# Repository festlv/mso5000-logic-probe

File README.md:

# MSO5000 logic analyzer probe

This project aims to be a somewhat lower performance but significantly cheaper alternative to Rigol's PLA2216 
logic analyzer probe for MSO5000-series oscilloscopes.

The project is based on the design published by Gandalf_Sr on [EEVBlog forum](https://www.eevblog.com/forum/testgear/ms05000-budget-logic-analyzer-probe-set-design/), 
with the most notable difference being that it should allow input signal threshold selection from the oscilloscope.

The project consists of two PCBs: 

* __connector-pcb__ which plugs into oscilloscope,
* 2x __probe-pcb__'s which connect to the aforementioned PCB via 24-pin IDC cables.

As the original design, it aims to support ~1-5V logic levels up to 100MHz. The probe PCBs can be built with 
two different TI level-shifters:

* SN74AXC8T245 with specified input range of 0.65-3.6V (4.2V abs. max).
* SN74**L**XC8T245 with specified input range of 1.1-5.5V (6.2V abs. max).

Do note that the propagation delay for lower input voltages can limit the observable signal's bandwidth!

## Current status

Revision 0 of both PCBAs has been assembled and passed basic function checks. The only required change was that series resistor
for ProbeDet signal was apparently too high (10K->100R).

Do keep in mind that the threshold level set in scope is not executed faitfhully- it's essentially amplified with a gain of 16.8
and provided as Vcc for SN74AXC8T245. See the datasheet of SN74AXC8T245 and connector-pcb/threshold-vcc-gain-calc.ods spreadsheet for details.

## Connector PCB

## Probe PCB

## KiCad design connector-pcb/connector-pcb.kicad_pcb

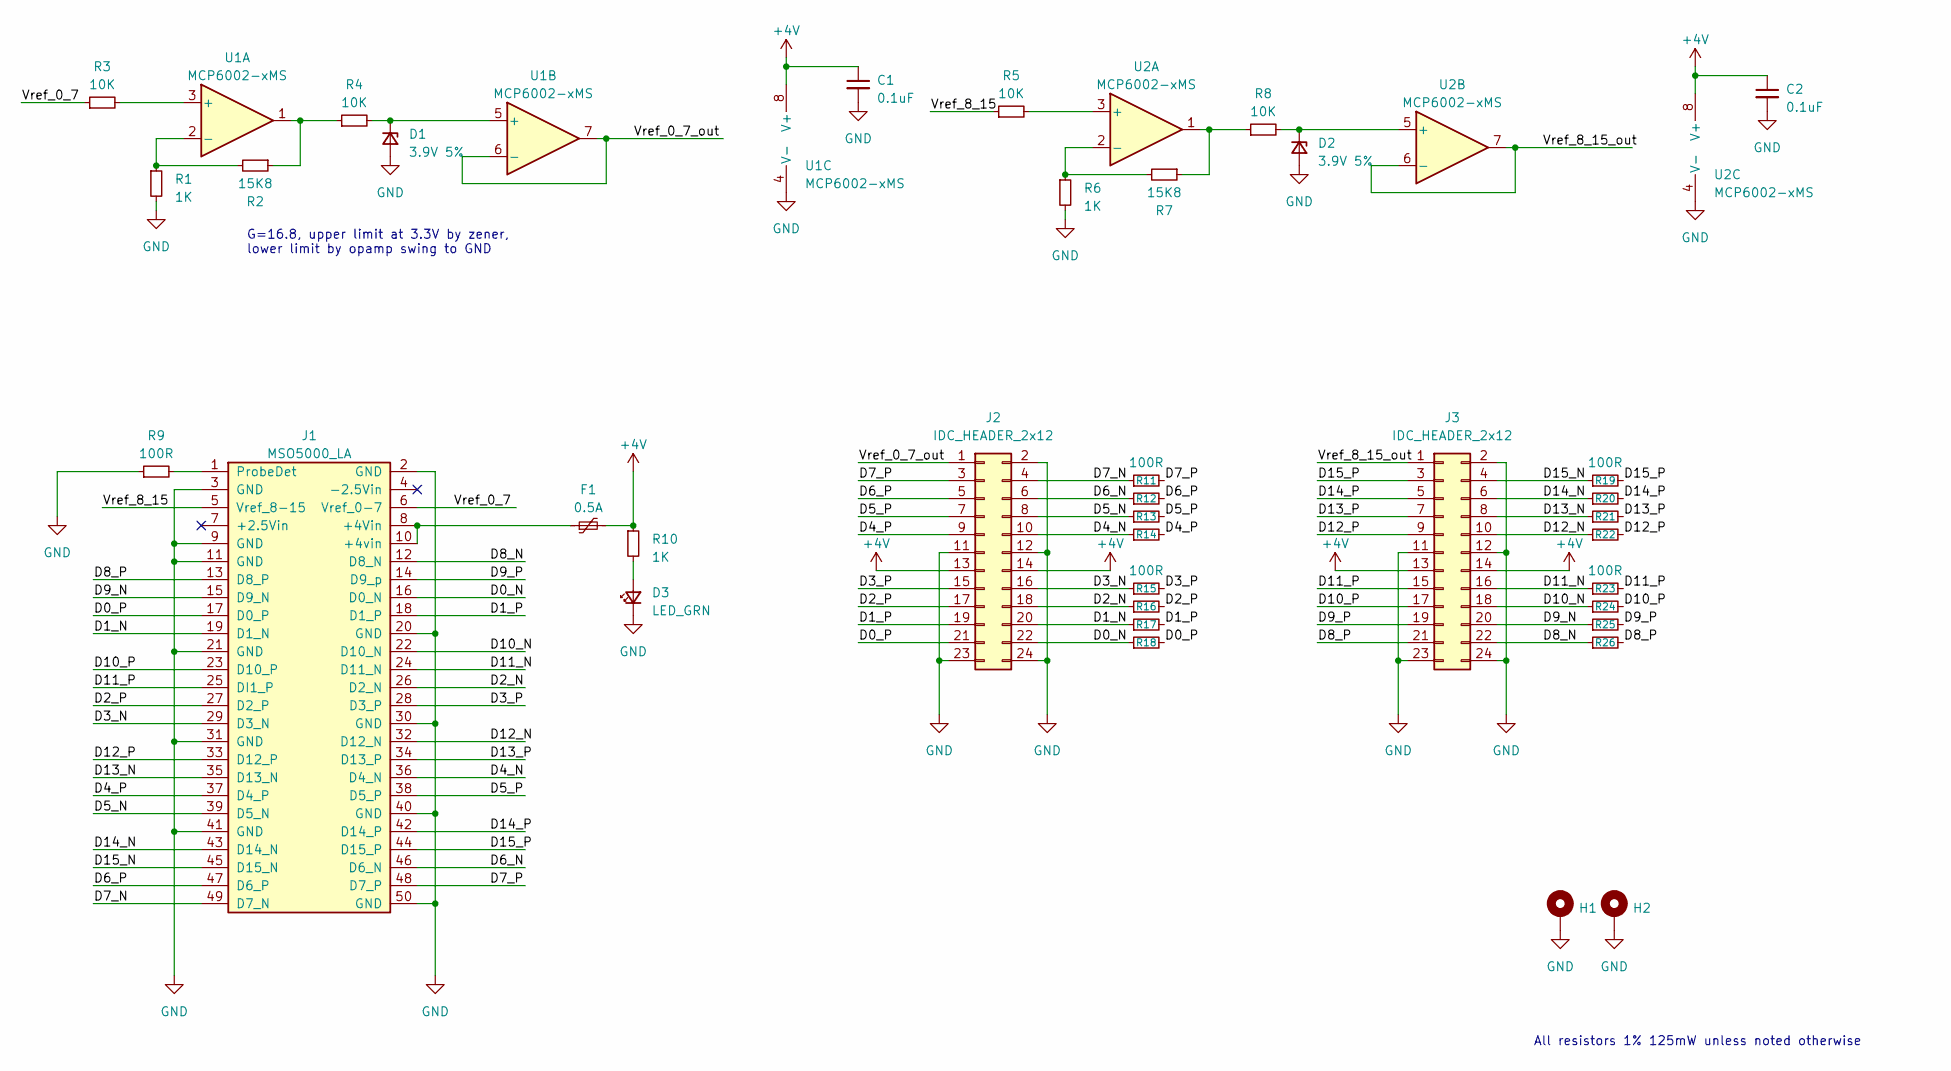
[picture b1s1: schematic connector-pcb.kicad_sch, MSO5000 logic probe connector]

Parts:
C1, C2: 0.1uF; C_0603_1608Metric; MPN CL10B104KB8NNNC; LCSC# C1591
D1, D2: 3.9V 5%; D_SOD-323; MPN MM3Z3V9; LCSC# C5359777
D3: LED_GRN; LED_0603_1608Metric; MPN XL-1608SYGC-06; LCSC# C965805
F1: 0.5A; Fuse_0603_1608Metric; MPN MF-FSMF020X-2; LCSC# C210356
H1, H2: MountingHole_Pad; MountingHole_3.2mm_M3_Pad_Via
J1: MSO5000_LA; PinSocket_2x25_P2.54mm_Horizontal; MPN SFH11-PBPC-D25-RA-BK
J2, J3: IDC_HEADER_2x12; IDC-Header_2x12_P2.54mm_Vertical; MPN B-3000S24P-0110; LCSC# C132440
R1, R6, R10: 1K; R_0603_1608Metric; MPN RC0603FR-071KL; LCSC# C22548
R2, R7: 15K8; R_0603_1608Metric; MPN RC0603FR-0715K8L; LCSC# C155689
R3, R4, R5, R8: 10K; R_0603_1608Metric; MPN RC0603FR-0710KL; LCSC# C98220
R9, R11, R12, R13, R14, R15, R16, R17, R18, R19, R20, R21, R22, R23, R24, R25, R26: 100R; R_0603_1608Metric; MPN RC0603FR-07100RL; LCSC# C105588
U1, U2: MCP6002-xMS; SOIC-8_3.9x4.9mm_P1.27mm; MPN MCP6002T-I/SN; LCSC# C7377

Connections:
+4V: C1.1, C2.1, F1.2, J2.13, J2.14, J3.13, J3.14, R10.1, U1.8 (V+), U2.8 (V+)
/D0_N: J1.16 (D0_N), J2.22, R18.1
/D0_P: J1.17 (D0_P), J2.21, R18.2
/D1_N: J1.19 (D1_N), J2.20, R17.1
/D1_P: J1.18 (D1_P), J2.19, R17.2
/D2_N: J1.26 (D2_N), J2.18, R16.1
/D2_P: J1.27 (D2_P), J2.17, R16.2
/D3_N: J1.29 (D3_N), J2.16, R15.1
/D3_P: J1.28 (D3_P), J2.15, R15.2
/D4_N: J1.36 (D4_N), J2.10, R14.1
/D4_P: J1.37 (D4_P), J2.9, R14.2
/D5_N: J1.39 (D5_N), J2.8, R13.1
/D5_P: J1.38 (D5_P), J2.7, R13.2
/D6_N: J1.46 (D6_N), J2.6, R12.1
/D6_P: J1.47 (D6_P), J2.5, R12.2
/D7_N: J1.49 (D7_N), J2.4, R11.1
/D7_P: J1.48 (D7_P), J2.3, R11.2
/D8_N: J1.12 (D8_N), J3.22, R26.1
/D8_P: J1.13 (D8_P), J3.21, R26.2
/D9_N: J1.15 (D9_N), J3.20, R25.1
/D9_P: J1.14 (D9_p), J3.19, R25.2
/D10_N: J1.22 (D10_N), J3.18, R24.1
/D10_P: J1.23 (D10_P), J3.17, R24.2
/D11_N: J1.24 (D11_N), J3.16, R23.1
/D11_P: J1.25 (DI1_P), J3.15, R23.2
/D12_N: J1.32 (D12_N), J3.10, R22.1
/D12_P: J1.33 (D12_P), J3.9, R22.2
/D13_N: J1.35 (D13_N), J3.8, R21.1
/D13_P: J1.34 (D13_P), J3.7, R21.2
/D14_N: J1.43 (D14_N), J3.6, R20.1
/D14_P: J1.42 (D14_P), J3.5, R20.2
/D15_N: J1.45 (D15_N), J3.4, R19.1
/D15_P: J1.44 (D15_P), J3.3, R19.2
/Vref_0_7: J1.6 (Vref_0-7), R3.1
/Vref_0_7_out: J2.1, U1.6 (-), U1.7
/Vref_8_15: J1.5 (Vref_8-15), R5.1
/Vref_8_15_out: J3.1, U2.6 (-), U2.7
GND: C1.2, C2.2, D1.2 (A), D2.2 (A), D3.1 (K), H1.1, H2.1, J1.2 (GND), J1.3 (GND), J1.9 (GND), J1.11 (GND), J1.20 (GND), J1.21 (GND), J1.30 (GND), J1.31 (GND), J1.40 (GND), J1.41 (GND), J1.50 (GND), J2.2, J2.11, J2.12, J2.23, J2.24, J3.2, J3.11, J3.12, J3.23, J3.24, R1.2, R6.2, R9.1, U1.4 (V-), U2.4 (V-)
unnamed: D1.1 (K), R4.2, U1.5 (+)
unnamed: D2.1 (K), R8.2, U2.5 (+)
unnamed: D3.2 (A), R10.2
unnamed: F1.1, J1.8 (+4Vin), J1.10 (+4vin)
unnamed: J1.1 (ProbeDet), R9.2
unnamed: R2.1, R4.1, U1.1
unnamed: R7.1, R8.1, U2.1
unnamed: R3.2, U1.3 (+)
unnamed: R1.1, R2.2, U1.2 (-)
unnamed: R5.2, U2.3 (+)
unnamed: R6.1, R7.2, U2.2 (-)

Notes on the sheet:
G=16.8, upper limit at 3.3V by zener, lower limit by opamp swing to GND
All resistors 1% 125mW unless noted otherwise

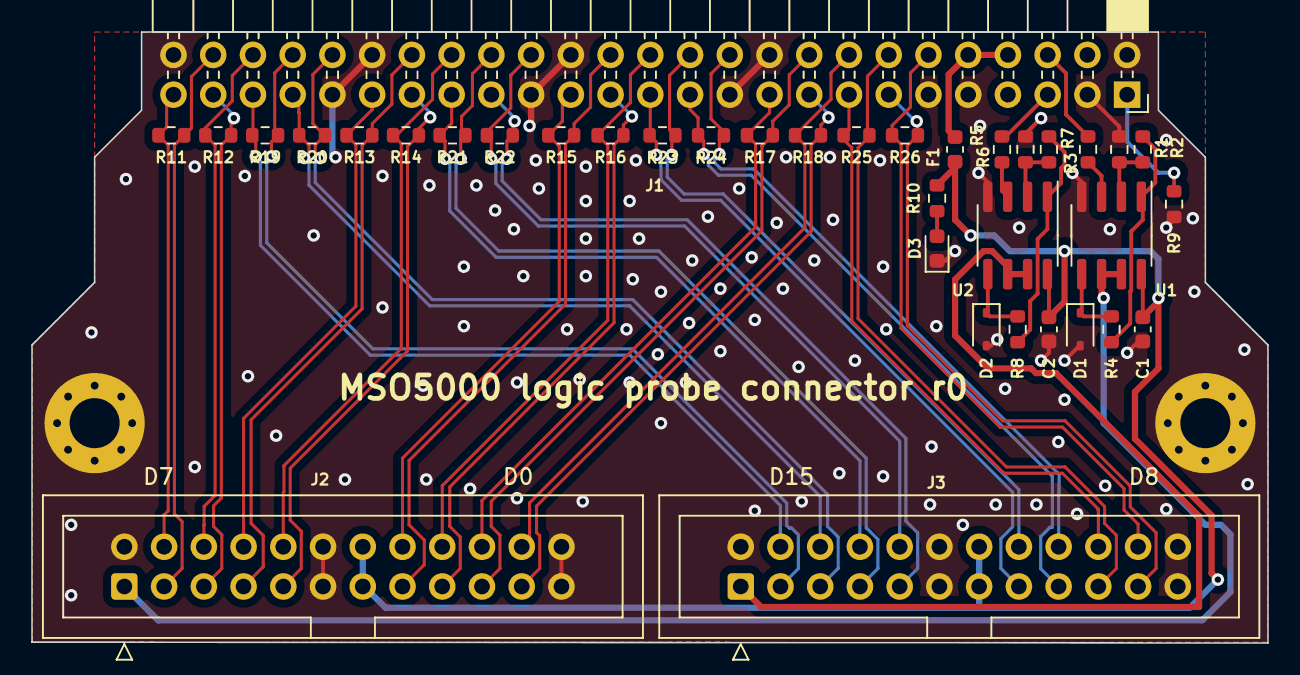
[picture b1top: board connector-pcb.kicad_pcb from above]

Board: 4 copper layers, 79.0 x 39.0 mm, 39 parts (0 on the bottom side), 49 nets.

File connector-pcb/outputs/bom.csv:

"Source:","/home/reinis/personal/mso5000-logic/connector-pcb/connector-pcb.kicad_sch"
"Date:","Tue 11 Apr 2023 07:54:40 PM EEST"
"Tool:","Eeschema 7.0.1"
"Generator:","/usr/share/kicad/plugins/bom_csv_grouped_by_value.py"
"Component Count:","37"

"Collated Components:"

"Item","Qty","Reference(s)","Value","LibPart","Footprint","Datasheet","DNP","LCSC#","MPN","Manufacturer"
"1","2","C1, C2","0.1uF","Device:C_Small","Capacitor_SMD:C_0603_1608Metric","~","","C1591","CL10B104KB8NNNC","Samsung Electro-Mechanics"
"2","2","D1, D2","3.9V 5%","Device:D_Zener_Small","Diode_SMD:D_SOD-323","~","","C5359777","MM3Z3V9","Fosan"
"3","1","D3","LED_GRN","Device:LED_Small","LED_SMD:LED_0603_1608Metric","~","","C965805","XL-1608SYGC-06","XINGLIGHT"
"4","1","F1","0.5A","Device:Polyfuse_Small","Fuse:Fuse_0603_1608Metric","~","","C210356","MF-FSMF020X-2","BOURNS"
"5","1","J1","MSO5000_LA","mso5000:MSO5000_LA","Connector_PinSocket_2.54mm:PinSocket_2x25_P2.54mm_Horizontal","~","","","SFH11-PBPC-D25-RA-BK","Sullins Connector Solutions"
"6","2","J2, J3","IDC_HEADER_2x12","Connector_Generic:Conn_02x12_Odd_Even","idc:IDC-Header_2x12_P2.54mm_Vertical","~","","C132440","B-3000S24P-0110","Ckmtw(Shenzhen Cankemeng)"
"7","3","R1, R6, R10","1K","Device:R_Small","Resistor_SMD:R_0603_1608Metric","~","","C22548","RC0603FR-071KL","YAGEO"
"8","2","R2, R7","15K8","Device:R_Small","Resistor_SMD:R_0603_1608Metric","~","","C155689","RC0603FR-0715K8L","YAGEO"
"9","4","R3, R4, R5, R8","10K","Device:R_Small","Resistor_SMD:R_0603_1608Metric","~","","C98220","RC0603FR-0710KL","YAGEO"
"10","17","R9, R11, R12, R13, R14, R15, R16, R17, R18, R19, R20, R21, R22, R23, R24, R25, R26","100R","Device:R_Small","Resistor_SMD:R_0603_1608Metric","~","","C105588","RC0603FR-07100RL","YAGEO"
"11","2","U1, U2","MCP6002-xMS","Amplifier_Operational:MCP6002-xMS","Package_SO:SOIC-8_3.9x4.9mm_P1.27mm","http://ww1.microchip.com/downloads/en/DeviceDoc/21733j.pdf","","C7377","MCP6002T-I/SN","Microchip"

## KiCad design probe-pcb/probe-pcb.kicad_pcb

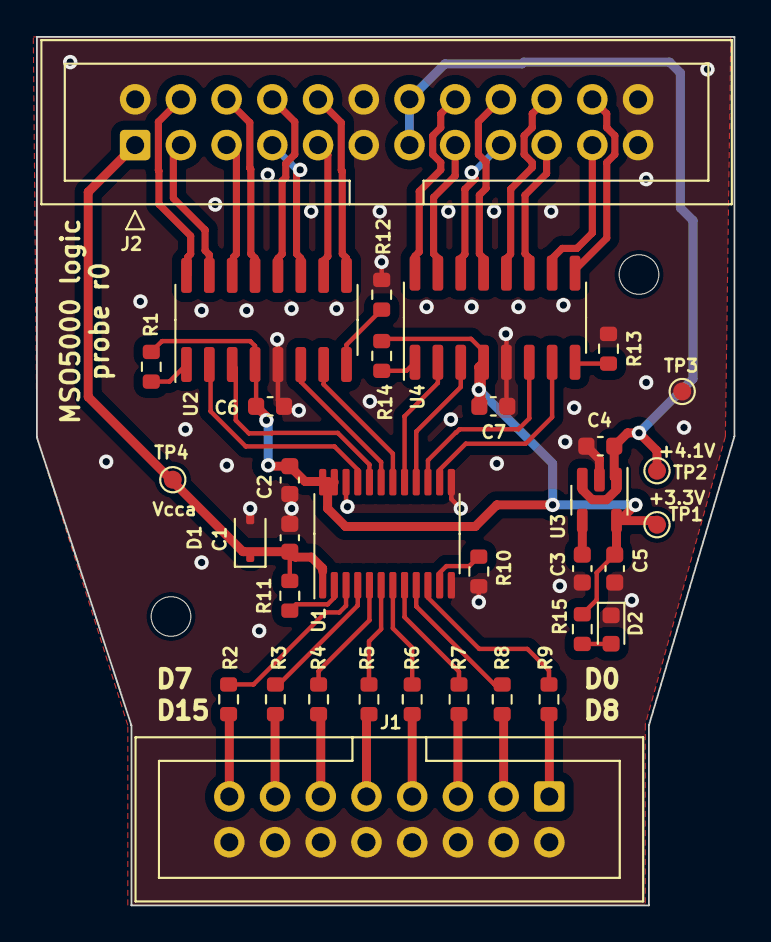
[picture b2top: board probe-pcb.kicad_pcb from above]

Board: 2 copper layers, 38.8 x 48.2 mm, 36 parts (0 on the bottom side), 52 nets.

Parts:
C1, C2, C6, C7: 0.1uF; C_0603_1608Metric
C3: 470pF; C_0603_1608Metric
C4, C5: 2.2uF; C_0603_1608Metric
D1: 3.9V 5%; D_SOD-323
D2: LED_GRN; LED_0603_1608Metric
H1, H2: MountingHole; MountingHole_2.2mm_M2
J1: IDC_HEADER_02x08; IDC-Header_2x08_P2.54mm_Vertical
J2: IDC_HEADER_2x12; IDC-Header_2x12_P2.54mm_Vertical
R1, R10, R11, R12, R13, R14: 0R; R_0603_1608Metric
R2, R3, R4, R5, R6, R7, R8, R9: 100R; R_0603_1608Metric
R15: 1K; R_0603_1608Metric
TP1, TP2, TP3, TP4: TP_1MM; TestPoint_Pad_D1.0mm
U1: SN74AXC8T245; TSSOP-24_4.4x7.8mm_P0.65mm
U2, U4: DS90LV047A; SOIC-16_3.9x9.9mm_P1.27mm
U3: MIC5205-3.3YM5; SOT-23-5

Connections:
+3V3: C2.1, C5.1, C6.1, C7.1, R1.1, R14.1, R15.1, TP1.1, U1.23 (VCCB), U1.24 (VCCB), U2.4 (VCC), U3.5 (OUT), U4.4 (VCC)
+4V: C4.1, J2.13, J2.14, TP2.1, U3.1 (IN), U3.3 (EN)
/D0: J1.1, R9.1
/D0_N: J2.22, U4.9 (DO-4)
/D0_P: J2.21, U4.10 (DO+4)
/D1: J1.3, R8.1
/D1_N: J2.20, U4.12 (DO-3)
/D1_P: J2.19, U4.11 (DO+3)
/D2: J1.5, R7.1
/D2_N: J2.18, U4.13 (DO-2)
/D2_P: J2.17, U4.14 (DO+2)
/D3: J1.7, R6.1
/D3_N: J2.16, U4.16 (DO-1)
/D3_P: J2.15, U4.15 (DO+1)
/D4: J1.9, R5.1
/D4_N: J2.10, U2.9 (DO-4)
/D4_P: J2.9, U2.10 (DO+4)
/D5: J1.11, R4.1
/D5_N: J2.8, U2.12 (DO-3)
/D5_P: J2.7, U2.11 (DO+3)
/D6: J1.13, R3.1
/D6_N: J2.6, U2.13 (DO-2)
/D6_P: J2.5, U2.14 (DO+2)
/D7: J1.15, R2.1
/D7_N: J2.4, U2.16 (DO-1)
/D7_P: J2.3, U2.15 (DO+1)
GND: C1.2, C2.2, C3.2, C4.2, C5.2, C6.2, C7.2, D1.2 (A), D2.1 (K), J1.2, J1.4, J1.6, J1.8, J1.10, J1.12, J1.14, J1.16, J2.2, J2.11, J2.12, J2.23, J2.24, R10.1, R12.1, R13.1, TP3.1, U1.12 (GND), U1.13 (GND), U1.22 (/OE), U2.5 (GND), U3.2 (GND), U4.5 (GND)
unnamed: D2.2 (A), R15.2
unnamed: R2.2, U1.3 (A1)
unnamed: R3.2, U1.4 (A2)
unnamed: R4.2, U1.5 (A3)
unnamed: R5.2, U1.6 (A4)
unnamed: R6.2, U1.7 (A5)
unnamed: R7.2, U1.8 (A6)
unnamed: R8.2, U1.9 (A7)
unnamed: R9.2, U1.10 (A8)
unnamed: U1.21 (B1), U2.2 (DI1)
unnamed: U1.20 (B2), U2.3 (DI2)
unnamed: U1.19 (B3), U2.6 (DI3)
unnamed: U1.18 (B4), U2.7 (DI4)
unnamed: U1.17 (B5), U4.2 (DI1)
unnamed: U1.16 (B6), U4.3 (DI2)
unnamed: U1.15 (B7), U4.6 (DI3)
unnamed: U1.14 (B8), U4.7 (DI4)
unnamed: R11.1, U1.2 (Dir1)
unnamed: R10.2, U1.11 (Dir2)
unnamed: R1.2, U2.1 (EN)
unnamed: R12.2, U2.8 (EN*)
unnamed: C3.1, U3.4 (BP)
unnamed: R14.2, U4.1 (EN)
unnamed: R13.2, U4.8 (EN*)
VCC: C1.1, D1.1 (K), J2.1, R11.2, TP4.1, U1.1 (VCCA)

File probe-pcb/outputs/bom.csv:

"Source:","/home/reinis/personal/mso5000-logic/probe-pcb/probe-pcb.kicad_sch"
"Date:","Sat 18 Mar 2023 02:10:12 AM EET"
"Tool:","Eeschema 7.0.1"
"Generator:","/usr/share/kicad/plugins/bom_csv_grouped_by_value.py"
"Component Count:","36"

"Collated Components:"

"Item","Qty","Reference(s)","Value","LibPart","Footprint","Datasheet","DNP","AltMPN","AltManufacturer","LCSC#","MPN","Manufacturer"
"1","4","C1, C2, C6, C7","0.1uF","Device:C_Small","Capacitor_SMD:C_0603_1608Metric","~","","","","C1591","CL10B104KB8NNNC","Samsung Electro-Mechanics"
"2","1","C3","470pF","Device:C_Small","Capacitor_SMD:C_0603_1608Metric","~","","","","C107092","CC0603KRX7R9BB471","YAGEO"
"3","2","C4, C5","2.2uF","Device:C_Small","Capacitor_SMD:C_0603_1608Metric","~","","","","C1607","CL10A225KP8NNNC","Samsung Electro-Mechanics"
"4","1","D1","3.9V 5%","Device:D_Zener_Small","Diode_SMD:D_SOD-323","~","","","","C5359777","MM3Z3V9","Fosan"
"5","1","D2","LED_GRN","Device:LED_Small","LED_SMD:LED_0603_1608Metric","~","","","","C965805","XL-1608SYGC-06","XINGLIGHT"
"6","2","H1, H2","MountingHole","Mechanical:MountingHole","MountingHole:MountingHole_2.2mm_M2","~","","","","","",""
"7","1","J1","IDC_HEADER_02x08","Connector_Generic:Conn_02x08_Odd_Even","Connector_IDC:IDC-Header_2x08_P2.54mm_Vertical","~","","","","C132430","B-3000S16P-0110","Ckmtw(Shenzhen Cankemeng)"
"8","1","J2","IDC_HEADER_2x12","Connector_Generic:Conn_02x12_Odd_Even","idc:IDC-Header_2x12_P2.54mm_Vertical","~","","","","C132440","B-3000S24P-0110","Ckmtw(Shenzhen Cankemeng)"
"9","6","R1, R10, R11, R12, R13, R14","0R","Device:R_Small","Resistor_SMD:R_0603_1608Metric","~","","","","C95177","RC0603JR-070RL","YAGEO"
"10","8","R2, R3, R4, R5, R6, R7, R8, R9","100R","Device:R_Small","Resistor_SMD:R_0603_1608Metric","~","","","","C105588","RC0603FR-07100RL","YAGEO"
"11","1","R15","1K","Device:R_Small","Resistor_SMD:R_0603_1608Metric","~","","","","C22548","RC0603FR-071KL","YAGEO"
"12","4","TP1, TP2, TP3, TP4","TP_1MM","Connector:TestPoint","TestPoint:TestPoint_Pad_D1.0mm","~","","","","","",""
"13","1","U1","SN74AXC8T245","mso5000:SN74AXC8T245","Package_SO:TSSOP-24_4.4x7.8mm_P0.65mm","https://www.ti.com/lit/ds/symlink/sn74axc8t245.pdf?ts=1678888996176","","SN74LXC8T245QPWRQ1","","C882718","SN74AXC8T245PWR","TI"
"14","2","U2, U4","DS90LV047A","mso5000:DS90LV047A","Package_SO:SOIC-16_3.9x9.9mm_P1.27mm","http://www.ti.com/lit/ds/symlink/ds90lv027a.pdf","","","","C206491","DS90LV047ATMX/NOPB","TI"
"15","1","U3","MIC5205-3.3YM5","Regulator_Linear:MIC5205-3.3YM5","Package_TO_SOT_SMD:SOT-23-5","http://ww1.microchip.com/downloads/en/DeviceDoc/20005785A.pdf","","TJ5205SF5-3.3","HTC Korea TAEJIN Tech","C126090","MIC5205-3.3YM5-TR","Microchip"

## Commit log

2023-03-16 Add r0 of connector PCB
2023-03-17 Change connector PCB to 4 layer board, finalize probe board
2023-03-17 Add 3d model for 2x12 pin header (missing in kicad library), add readme
2023-03-18 Change zener diodes to 3.9V (should protect both 3.3V and 5V level shifters)
2023-04-11 Changed R9 of connector PCB from 10k to 100R (otherwise the scope wouldn't detect the probes)
2023-04-11 Update readme with status of testing and pics of assembled boards
